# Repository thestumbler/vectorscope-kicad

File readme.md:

# Hackaday Supercon 2023 Vectorscope 
### KiCad Redrawing Project

This is a port of the Vectorscope schematics into KiCad. 
It is also a partially-complete KiCad project using Voja Antonic's original 
Circuit Maker PCB design as converted into KiCad PCB format by Thomas Flummer.

## Status

* Schematics created, first pass error checking complete. It has not been
meticulously compared with the original schematics.

* Symbols have been collected into a single project library:
  `vector.kicad_sym`

* New footprints, as needed, will go into a single project library:
  `vector.pretty`

* Original footprints extracted from the PCB and stored into a single
  project library: `vector-orig.pretty`

* So far, the changes to the original converted PCB are minimal and
  coule be easily replicated should the Circuit Maker design be updated:
  - footprints changed to point to `vector-orig.pretty`
  - graphical lines converted to KiCad PCB traces

## Issues

#### PCB Changes, traces

As noted above, the circuit traces on the PCB, as converted, are just
graphical lines. These can easily be changed into PCB traces using the
built-in `Create Tracks from Selection` option (Kicad v7).

#### PCB Changes, footprints (TBD)

Some parts in the PCB don't have the expected footprints, but are instead just
a collection of features. For example, the three each 0.1 inch IO pin-header 
connectors appear instead as 20 separate "footprints", each one a single
pad. I have investigated how to fix these, and it is pretty straightfoward:

* IO connectors, 
  - Scope Input, 1x4
  - Signal Generator Output, 1x4
  - IO Connector, 1x12
* Speaker
* Two SMT test pads (external power?)
* Slide switch
* Battery holders

#### Schematics

The following errors have been identified in the original schematics:

* Capacitor C16 seems to be duplicated (not 100% confirmed)
* TPA321 Speaker amplifier connects to +3V3, not +3V3F
* Some not-connected Pico pins are not shown on the original

#### Part Footprint Mismatches

Several discrete parts in the original PCB file are not consistent
between three different sources: the footprint itself, the assocaited 3D
file, and the real part as idenified in the BOM. These are as follows:

* LEDs
  - footprint: 0603
  - 3D file: 0603 
  - BOM: 0805 

* Resistors
  - footprint: Tantalum Kemet C (note 1)
  - 3D file: 0603
  - BOM 0805

* Capacitors, 2.2uF and 100nF
  - footprint: Tantalum Kemet C (note 1)
  - 3D file: 0603
  - BOM 0603

* Capacitors, 22uF
  - footprint: Voja custom part
  - 3D file: EIA 3528/Kemet T (note 2)
  - BOM: 1210

Note 1: The Tantalum Kemet C package is EIA 6023, which about the size 
of an EIA 2512 resistor. 

Note 2: Tantalum Kemet T packate is EIA 3528, which is a bit largeer than
an EIA 1210 resistor.

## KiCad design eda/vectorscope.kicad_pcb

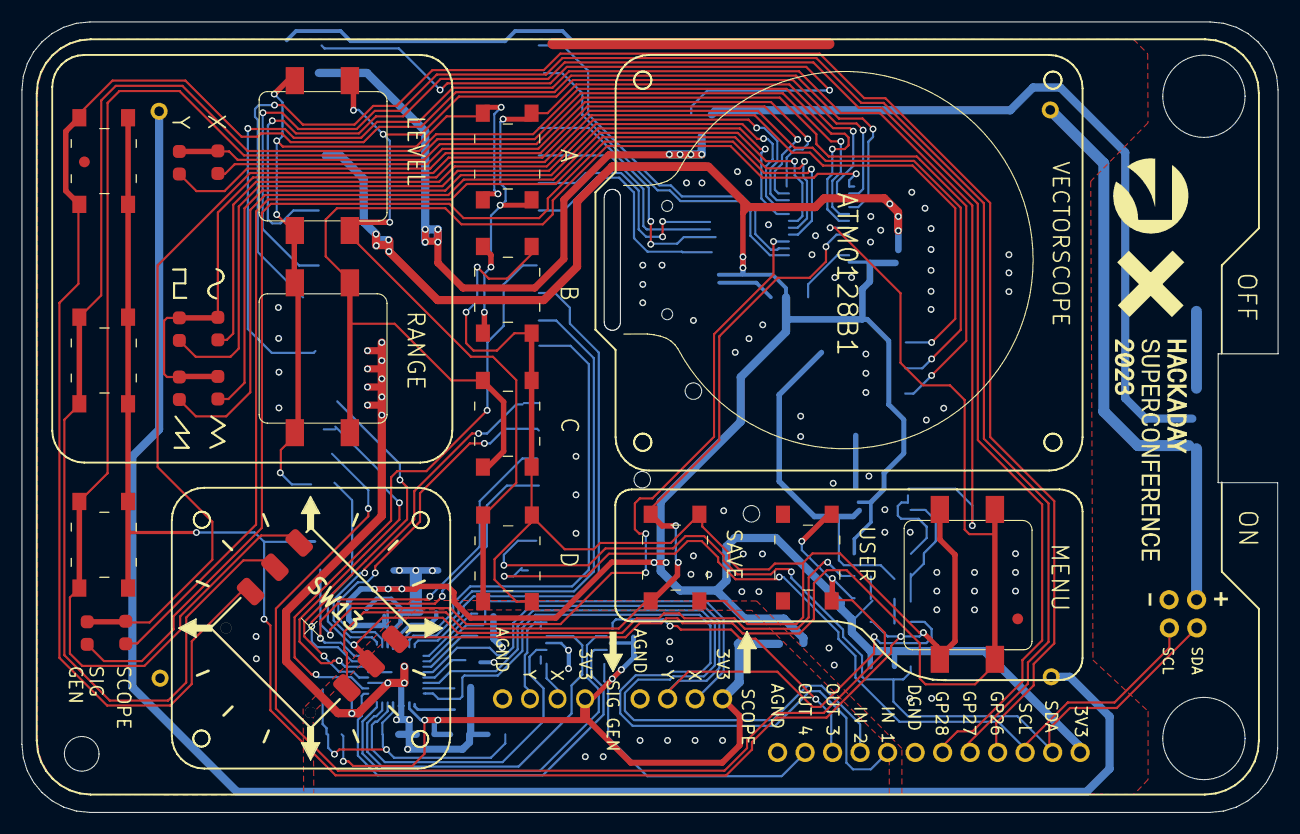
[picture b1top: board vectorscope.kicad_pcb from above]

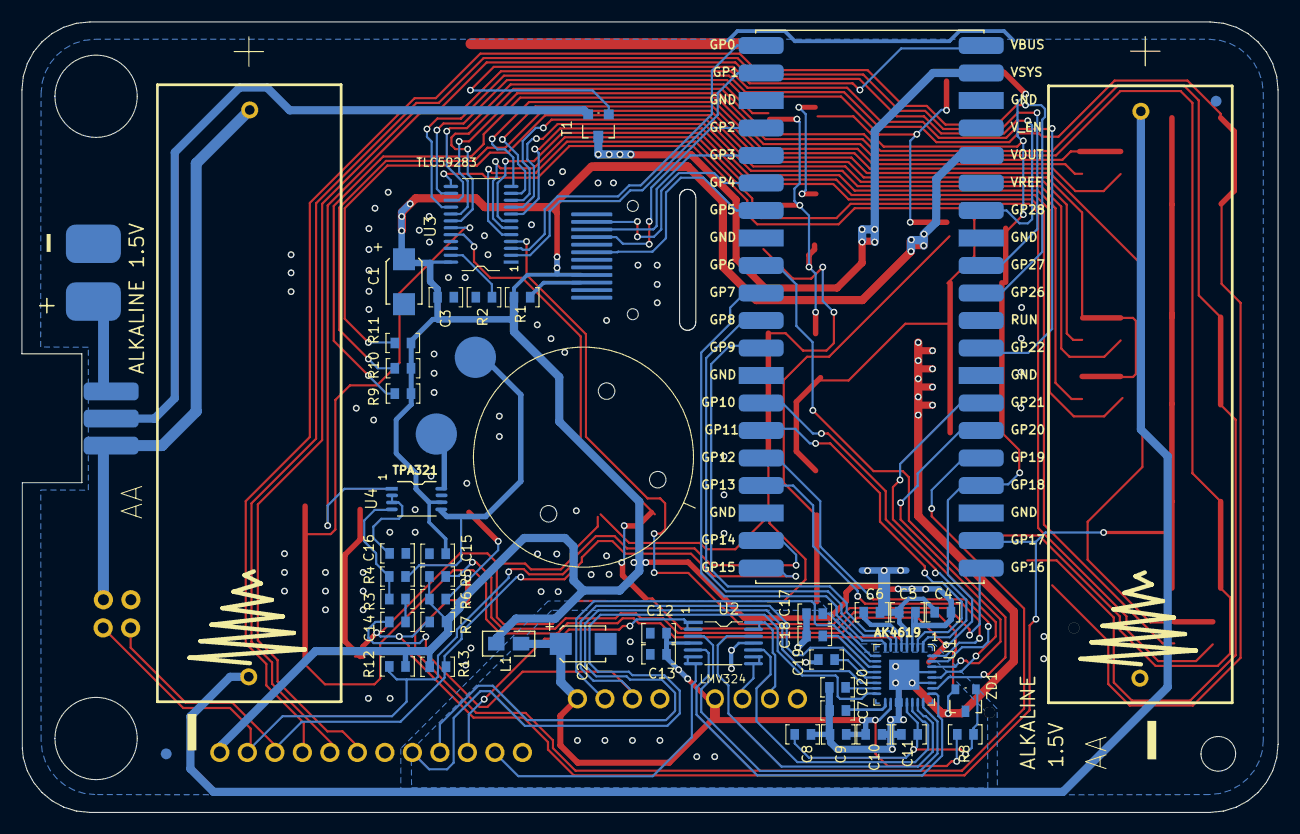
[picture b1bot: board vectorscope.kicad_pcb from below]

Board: 2 copper layers, 116.0 x 73.0 mm, 62 parts (41 on the bottom side), 2 nets.

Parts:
C1, C2: 22uF; _Users_Voja_Desktop_Projekti_Gio.PcbLib_Tantal
C3, C4, C10, C11, C13, C14, C17, C18, C19, C20: 100nF; _Users_Voja_Desktop_CUBE_ESP.PcbLib_TANTALUM KEMET C
C5, C6, C7, C8, C9, C12, C15, C16: 2u2; _Users_Voja_Desktop_CUBE_ESP.PcbLib_TANTALUM KEMET C
L1: 100nF; 0805
LY1, LY2, LY3, LY4, LY5, LY6, LY7, LY8: _Users_Voja_Desktop_ESP.PcbLib_LED0603
M1: PICO; _Users_Voja_Desktop_Projekti_Gio.PcbLib_PICO
R1: 22R; _Users_Voja_Desktop_CUBE_ESP.PcbLib_TANTALUM KEMET C
R2, R12, R13: 2K7; _Users_Voja_Desktop_CUBE_ESP.PcbLib_TANTALUM KEMET C
R3: 47K; _Users_Voja_Desktop_CUBE_ESP.PcbLib_TANTALUM KEMET C
R4: 22K; _Users_Voja_Desktop_CUBE_ESP.PcbLib_TANTALUM KEMET C
R5, R6, R7: 4K7; _Users_Voja_Desktop_CUBE_ESP.PcbLib_TANTALUM KEMET C
R8: 82R; _Users_Voja_Desktop_CUBE_ESP.PcbLib_TANTALUM KEMET C
R9, R10, R11: 330R; _Users_Voja_Desktop_CUBE_ESP.PcbLib_TANTALUM KEMET C
SW1, SW2, SW3, SW4, SW5, SW6, SW7, SW8, SW9: tactile key; _Users_Voja_Documents_GitHub_willo-pcb_ESP.PcbLib_key4p
SW10, SW11, SW12: Comment; key 12x12 SMD
SW13: Comment; _Users_Voja_Desktop_Projekti_Gio.PcbLib_JOYSTICK 2
T1: DMN65D8L-7; SOT-23
U1: AK4619
U2: LMV324; TSSOP 14
U3: TLC59283; _Users_Voja_Desktop_Projekti_Gio.PcbLib_TQFN24
U4: TPA321; _Users_Voja_Desktop_CUBE_ESP.PcbLib_MSOP8
ZD1: LM4040; SOT-23

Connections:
AGND: C2.-, U1.CAD/CSN, U1.SI, U1.VREFL, U1.VSS1, U2.GND, ZD1.2
GND: C1.-, M1.AGND, M1.GND, U3.GND, U3.OE, U4.GND

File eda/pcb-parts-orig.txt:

[NoRef]	[NoVal]	vector-orig:
[NoRef]	[NoVal]	vector-orig:
SW12	Comment	vector-orig:key 12x12 SMD
[NoRef]	[NoVal]	vector-orig:
[NoRef]	[NoVal]	vector-orig:
[NoRef]	[NoVal]	vector-orig:
[NoRef]	[NoVal]	vector-orig:
[NoRef]	[NoVal]	vector-orig:
[NoRef]	[NoVal]	vector-orig:
SW5	tactile key	vector-orig:_Users_Voja_Documents_GitHub_willo-pcb_ESP.PcbLib_key4p
[NoRef]	[NoVal]	vector-orig:
[NoRef]	[NoVal]	vector-orig:
LY4	[NoVal]	vector-orig:_Users_Voja_Desktop_ESP.PcbLib_LED0603
LY3	[NoVal]	vector-orig:_Users_Voja_Desktop_ESP.PcbLib_LED0603
[NoRef]	[NoVal]	vector-orig:
[NoRef]	[NoVal]	vector-orig:
[NoRef]	[NoVal]	vector-orig:
SW6	tactile key	vector-orig:_Users_Voja_Documents_GitHub_willo-pcb_ESP.PcbLib_key4p
SW9	tactile key	vector-orig:_Users_Voja_Documents_GitHub_willo-pcb_ESP.PcbLib_key4p
[NoRef]	[NoVal]	vector-orig:
[NoRef]	[NoVal]	vector-orig:
LY8	[NoVal]	vector-orig:_Users_Voja_Desktop_ESP.PcbLib_LED0603
SW13	Comment	vector-orig:_Users_Voja_Desktop_Projekti_Gio.PcbLib_JOYSTICK 2
[NoRef]	[NoVal]	vector-orig:
[NoRef]	[NoVal]	vector-orig:
SW3	tactile key	vector-orig:_Users_Voja_Documents_GitHub_willo-pcb_ESP.PcbLib_key4p
[NoRef]	[NoVal]	vector-orig:
[NoRef]	[NoVal]	vector-orig:
SW8	tactile key	vector-orig:_Users_Voja_Documents_GitHub_willo-pcb_ESP.PcbLib_key4p
[NoRef]	[NoVal]	vector-orig:
[NoRef]	[NoVal]	vector-orig:
SW4	tactile key	vector-orig:_Users_Voja_Documents_GitHub_willo-pcb_ESP.PcbLib_key4p
[NoRef]	[NoVal]	vector-orig:
[NoRef]	[NoVal]	vector-orig:
LY1	[NoVal]	vector-orig:_Users_Voja_Desktop_ESP.PcbLib_LED0603
[NoRef]	[NoVal]	vector-orig:
[NoRef]	[NoVal]	vector-orig:
[NoRef]	[NoVal]	vector-orig:
[NoRef]	[NoVal]	vector-orig:
[NoRef]	[NoVal]	vector-orig:
[NoRef]	[NoVal]	vector-orig:
[NoRef]	[NoVal]	vector-orig:
SW2	tactile key	vector-orig:_Users_Voja_Documents_GitHub_willo-pcb_ESP.PcbLib_key4p
[NoRef]	[NoVal]	vector-orig:
SW7	tactile key	vector-orig:_Users_Voja_Documents_GitHub_willo-pcb_ESP.PcbLib_key4p
[NoRef]	[NoVal]	vector-orig:
[NoRef]	[NoVal]	vector-orig:
[NoRef]	[NoVal]	vector-orig:
[NoRef]	[NoVal]	vector-orig:
LY2	[NoVal]	vector-orig:_Users_Voja_Desktop_ESP.PcbLib_LED0603
[NoRef]	[NoVal]	vector-orig:
[NoRef]	[NoVal]	vector-orig:
[NoRef]	[NoVal]	vector-orig:
[NoRef]	[NoVal]	vector-orig:
[NoRef]	[NoVal]	vector-orig:
[NoRef]	[NoVal]	vector-orig:
[NoRef]	[NoVal]	vector-orig:
[NoRef]	[NoVal]	vector-orig:
LY5	[NoVal]	vector-orig:_Users_Voja_Desktop_ESP.PcbLib_LED0603
LY6	[NoVal]	vector-orig:_Users_Voja_Desktop_ESP.PcbLib_LED0603
SW1	tactile key	vector-orig:_Users_Voja_Documents_GitHub_willo-pcb_ESP.PcbLib_key4p
[NoRef]	[NoVal]	vector-orig:
[NoRef]	[NoVal]	vector-orig:
[NoRef]	[NoVal]	vector-orig:
LY7	[NoVal]	vector-orig:_Users_Voja_Desktop_ESP.PcbLib_LED0603
[NoRef]	[NoVal]	vector-orig:
[NoRef]	[NoVal]	vector-orig:
[NoRef]	[NoVal]	vector-orig:
[NoRef]	[NoVal]	vector-orig:
[NoRef]	[NoVal]	vector-orig:
[NoRef]	[NoVal]	vector-orig:
SW10	Comment	vector-orig:key 12x12 SMD
[NoRef]	[NoVal]	vector-orig:
[NoRef]	[NoVal]	vector-orig:
SW11	Comment	vector-orig:key 12x12 SMD
[NoRef]	[NoVal]	vector-orig:
[NoRef]	[NoVal]	vector-orig:
[NoRef]	[NoVal]	vector-orig:
[NoRef]	[NoVal]	vector-orig:
[NoRef]	[NoVal]	vector-orig:
C17	100nF	vector-orig:_Users_Voja_Desktop_CUBE_ESP.PcbLib_TANTALUM KEMET C
R6	4K7	vector-orig:_Users_Voja_Desktop_CUBE_ESP.PcbLib_TANTALUM KEMET C
M1	PICO	vector-orig:_Users_Voja_Desktop_Projekti_Gio.PcbLib_PICO
T1	DMN65D8L-7	vector-orig:SOT-23
R1	22R	vector-orig:_Users_Voja_Desktop_CUBE_ESP.PcbLib_TANTALUM KEMET C
C6	2u2	vector-orig:_Users_Voja_Desktop_CUBE_ESP.PcbLib_TANTALUM KEMET C
C15	2u2	vector-orig:_Users_Voja_Desktop_CUBE_ESP.PcbLib_TANTALUM KEMET C
C7	2u2	vector-orig:_Users_Voja_Desktop_CUBE_ESP.PcbLib_TANTALUM KEMET C
R7	4K7	vector-orig:_Users_Voja_Desktop_CUBE_ESP.PcbLib_TANTALUM KEMET C
R3	47K	vector-orig:_Users_Voja_Desktop_CUBE_ESP.PcbLib_TANTALUM KEMET C
L1	100nF	vector-orig:0805
R2	2K7	vector-orig:_Users_Voja_Desktop_CUBE_ESP.PcbLib_TANTALUM KEMET C
R8	82R	vector-orig:_Users_Voja_Desktop_CUBE_ESP.PcbLib_TANTALUM KEMET C
C1	22uF	vector-orig:_Users_Voja_Desktop_Projekti_Gio.PcbLib_Tantal
R9	330R	vector-orig:_Users_Voja_Desktop_CUBE_ESP.PcbLib_TANTALUM KEMET C
C5	2u2	vector-orig:_Users_Voja_Desktop_CUBE_ESP.PcbLib_TANTALUM KEMET C
C20	100nF	vector-orig:_Users_Voja_Desktop_CUBE_ESP.PcbLib_TANTALUM KEMET C
U4	TPA321	vector-orig:_Users_Voja_Desktop_CUBE_ESP.PcbLib_MSOP8
C18	100nF	vector-orig:_Users_Voja_Desktop_CUBE_ESP.PcbLib_TANTALUM KEMET C
R4	22K	vector-orig:_Users_Voja_Desktop_CUBE_ESP.PcbLib_TANTALUM KEMET C
C14	100nF	vector-orig:_Users_Voja_Desktop_CUBE_ESP.PcbLib_TANTALUM KEMET C
C8	2u2	vector-orig:_Users_Voja_Desktop_CUBE_ESP.PcbLib_TANTALUM KEMET C
C4	100nF	vector-orig:_Users_Voja_Desktop_CUBE_ESP.PcbLib_TANTALUM KEMET C
C12	2u2	vector-orig:_Users_Voja_Desktop_CUBE_ESP.PcbLib_TANTALUM KEMET C
R13	2K7	vector-orig:_Users_Voja_Desktop_CUBE_ESP.PcbLib_TANTALUM KEMET C
C9	2u2	vector-orig:_Users_Voja_Desktop_CUBE_ESP.PcbLib_TANTALUM KEMET C
C13	100nF	vector-orig:_Users_Voja_Desktop_CUBE_ESP.PcbLib_TANTALUM KEMET C
R11	330R	vector-orig:_Users_Voja_Desktop_CUBE_ESP.PcbLib_TANTALUM KEMET C
C16	2u2	vector-orig:_Users_Voja_Desktop_CUBE_ESP.PcbLib_TANTALUM KEMET C
C10	100nF	vector-orig:_Users_Voja_Desktop_CUBE_ESP.PcbLib_TANTALUM KEMET C
ZD1	LM4040	vector-orig:SOT-23
R12	2K7	vector-orig:_Users_Voja_Desktop_CUBE_ESP.PcbLib_TANTALUM KEMET C
R5	4K7	vector-orig:_Users_Voja_Desktop_CUBE_ESP.PcbLib_TANTALUM KEMET C
C19	100nF	vector-orig:_Users_Voja_Desktop_CUBE_ESP.PcbLib_TANTALUM KEMET C
U1	AK4619	vector-orig:AK4619
C2	22uF	vector-orig:_Users_Voja_Desktop_Projekti_Gio.PcbLib_Tantal
U2	LMV324	vector-orig:TSSOP 14
U3	TLC59283	vector-orig:_Users_Voja_Desktop_Projekti_Gio.PcbLib_TQFN24
C11	100nF	vector-orig:_Users_Voja_Desktop_CUBE_ESP.PcbLib_TANTALUM KEMET C
C3	100nF	vector-orig:_Users_Voja_Desktop_CUBE_ESP.PcbLib_TANTALUM KEMET C
R10	330R	vector-orig:_Users_Voja_Desktop_CUBE_ESP.PcbLib_TANTALUM KEMET C

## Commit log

2023-11-08 page templates
2023-11-08 wrapped up schematic entry
2023-11-08 added pdf
2023-11-08 restored original schematic pdf (accidentally overwrote last commit)
2023-11-08 added hackaday logo
2023-11-08 added USB cable to Pico
2023-11-09 edited readme
2023-11-09 cleaned up schematic some, solved some DRC errors
2023-11-09 all schematic symbols now in local project library
2023-11-10 cleaned up DRC schematic errors, assigned original footprints schematics
2023-11-10 moved image to top of readme
2023-11-10 fixed typo in footprint library name (missing dot, .vector-orig)
